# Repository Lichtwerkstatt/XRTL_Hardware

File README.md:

# XRTL_Hardware
Welcome to the XRTL Hardware repository! If you are trying to add actuators, sensors or cameras to your setup, you have come to the right place. You can jump right in and start building or head over to our [wiki](https://github.com/Lichtwerkstatt/XRTL_Hardware/wiki) for basic guides and more information on how to get your hardware to talk to your servers.

If you are instead looking for the software to build some servers or maybe some fancy UI, our [software repository](https://github.com/Lichtwerkstatt/XRTL_SPA) might be the right place for you.

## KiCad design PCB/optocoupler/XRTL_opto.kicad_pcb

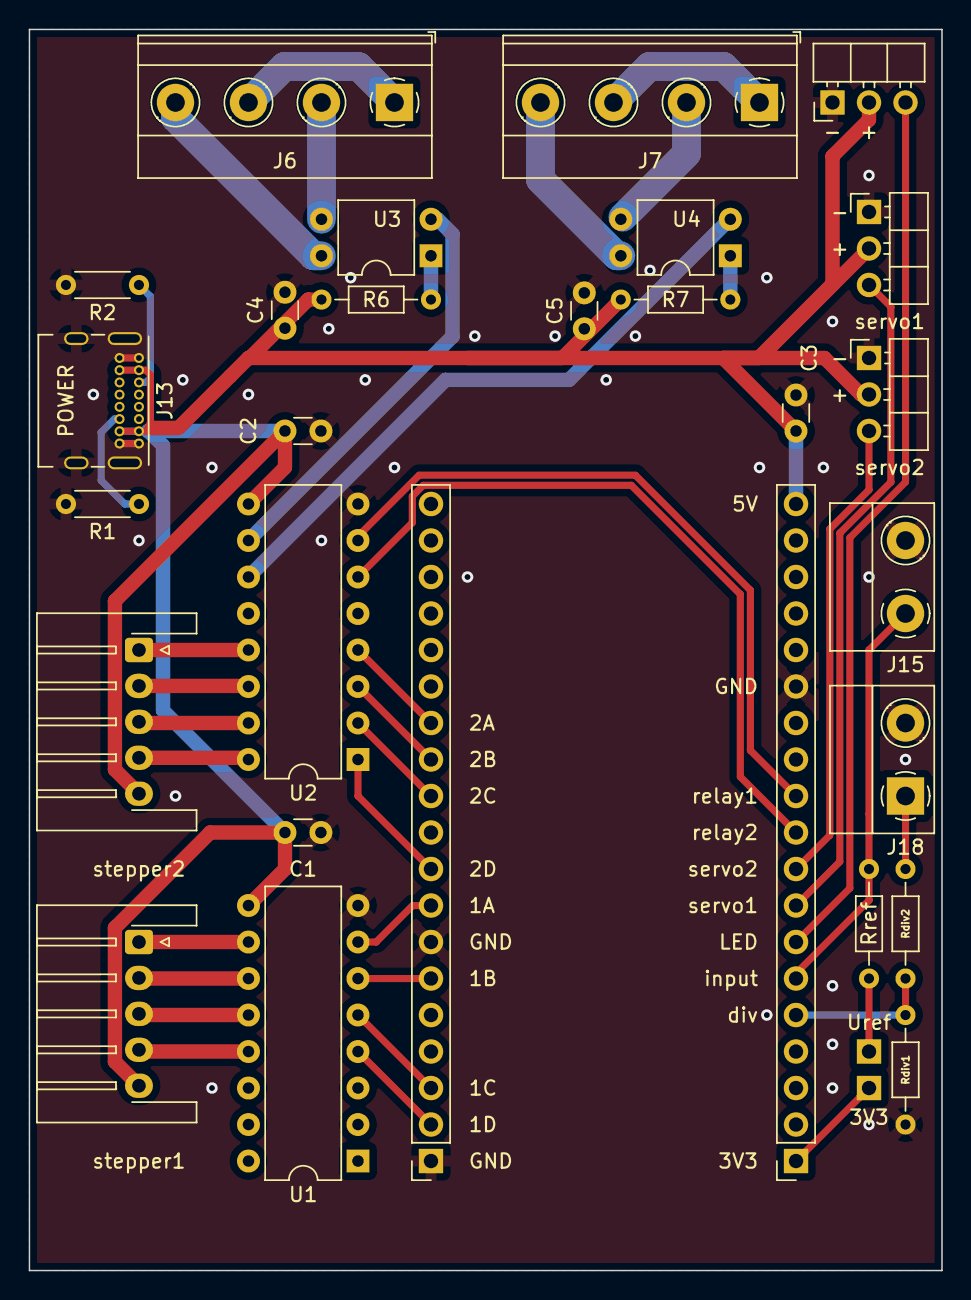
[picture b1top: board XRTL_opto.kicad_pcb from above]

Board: 2 copper layers, 63.5 x 86.4 mm, 30 parts (0 on the bottom side), 40 nets.

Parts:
3V3: conn; PinHeader_1x01_P2.54mm_Vertical
C1, C2, C3, C4, C5: 100n; C_Disc_D3.0mm_W1.6mm_P2.50mm
J2: stepper1; JST_XH_S5B-XH-A-1_1x05_P2.50mm_Horizontal
J3: stepper2; JST_XH_S5B-XH-A-1_1x05_P2.50mm_Horizontal
J4: ESP32 right; PinSocket_1x19_P2.54mm_Vertical
J5: ESP32 left; PinSocket_1x19_P2.54mm_Vertical
J6: relay2; TerminalBlock_Phoenix_MKDS-1,5-4-5.08_1x04_P5.08mm_Horizont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
J7: relay1; TerminalBlock_Phoenix_MKDS-1,5-4-5.08_1x04_P5.08mm_Horizont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
J10: servo1; PinHeader_1x03_P2.54mm_Horizontal
J11: servo2; PinHeader_1x03_P2.54mm_Horizontal
J12: infoLED; PinHeader_1x03_P2.54mm_Horizontal
J13: USBC_5V_3A_input; USB_C_Receptacle_GCT_USB4085
J15: input; TerminalBlock_Phoenix_MKDS-1,5-2-5.08_1x02_P5.08mm_Horizont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
J18: divider; TerminalBlock_Phoenix_MKDS-1,5-2-5.08_1x02_P5.08mm_Horizont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
R1, R2: 5.1k; R_Axial_DIN0204_L3.6mm_D1.6mm_P5.08mm_Horizontal
R6, R7: 511; R_Axial_DIN0204_L3.6mm_D1.6mm_P7.62mm_Horizontal
Rdiv1, Rdiv2: 3.00k; R_Axial_DIN0204_L3.6mm_D1.6mm_P7.62mm_Horizontal
Rref: 3.00k; R_Axial_DIN0204_L3.6mm_D1.6mm_P7.62mm_Horizontal
U1, U2: TBD62003; DIP-16_W7.62mm
U3, U4: TLP3553A; DIP-4_W7.62mm
Uref: Uref; PinHeader_1x01_P2.54mm_Vertical

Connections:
+3V3: 3V3.1, J4.1
+5V: C1.1, C2.1, C3.1, C4.1, C5.1, J2.5, J3.5, J4.19, J10.2, J11.2, J12.2, J13.A4 (VBUS), J13.A9 (VBUS), J13.B4 (VBUS), J13.B9 (VBUS), R6.1, R7.1, U1.9 (COM), U2.9 (COM)
GND: C1.2, C2.2, C3.2, C4.2, C5.2, J4.14, J5.1, J5.7, J10.1, J11.1, J12.1, J13.A1 (GND), J13.A12 (GND), J13.B1 (GND), J13.B12 (GND), J13.S1 (SHIELD), J15.2, J18.2, R1.2, R2.2, Rdiv1.1, U1.8 (GND), U2.8 (GND)
unnamed: J2.1, U1.10 (O7)
unnamed: J2.2, U1.11 (O6)
unnamed: J2.3, U1.12 (O5)
unnamed: J2.4, U1.13 (O4)
unnamed: J3.1, U2.13 (O4)
unnamed: J3.2, U2.14 (O3)
unnamed: J3.3, U2.15 (O2)
unnamed: J3.4, U2.16 (O1)
unnamed: J6.1, J6.3
unnamed: J6.2, U3.3
unnamed: J6.4, U3.4
unnamed: J7.1, J7.3
unnamed: J7.2, U4.3
unnamed: J7.4, U4.4
unnamed: J13.A5 (CC1), R2.1
unnamed: J13.B5 (CC2), R1.1
unnamed: Rref.2, Uref.1
unnamed: J18.1, Rdiv2.2
unnamed: R6.2, U3.1
unnamed: R7.2, U4.1
driverRelay1: U2.11 (O6), U4.2
driverRelay2: U2.10 (O7), U3.2
infoLED: J4.7, J12.3
input1: J4.6, J15.1, Rref.1
input2: J4.5, Rdiv1.2, Rdiv2.1
relay1: J4.11, U2.7 (I7)
relay2: J4.10, U2.6 (I6)
servo1: J4.8, J10.3
servo2: J4.9, J11.3
stepper1A: J5.8, U1.7 (I7)
stepper1B: J5.6, U1.6 (I6)
stepper1C: J5.3, U1.5 (I5)
stepper1D: J5.2, U1.4 (I4)
stepper2A: J5.13, U2.4 (I4)
stepper2B: J5.12, U2.3 (I3)
stepper2C: J5.11, U2.2 (I2)
stepper2D: J5.9, U2.1 (I1)

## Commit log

2021-11-19 entered legacy files
2021-12-03 Create socketIO-KM100.ino
    control single stepper motor via socketIO
2021-12-06 Update socketIO-KM100.ino
    new features:
    -second stepper motor
    -report state before and after moving
    -save current position to EEPROM before restart
2021-12-13 Update socketIO-KM100.ino
    migrate to non blocking stepper library <AccelStepper.h>
2021-12-13 Create ESP8266_ID25
    Controling an ID25 iris aperture via an ESP8266 using a single stepper motor
2021-12-13 Create socketIO-KM100-ESP8266.ino
    adjusted for use on ESP8266
2021-12-20 Update ESP8266_ID25
    -added settings file via LittleFS
    -saving and loading of settings from flash
    -set automatic WiFi reconnect
2021-12-20 Update ESP8266_ID25
2021-12-20 Update socketIO-KM100.ino
    -settings stored and loaded via LITTLEFS
    -automatic WiFi reconnect
2021-12-20 Update socketIO-KM100-ESP8266.ino
    -store settings in flash via LittleFS
    -automatic WiFi reconnect
2022-01-13 implemented automatic reconnect
2022-01-14 non blocking reconnect
2022-01-20 Create LICENSE
2022-01-20 unified ESP32/ESP8266 programs
2022-01-23 added Workshop Reference Markdown
2022-01-23 extended workshop file
2022-01-23 markdown is so nice! I never knew...
2022-01-24 updated workshop script webserver
2022-01-24 workshop file connectWifi
2022-01-24 workshop scripts MQTT
2022-01-24 found text highlightning
2022-01-24 update highlights
2022-01-25 updated workflow
2022-01-25 updated HTTP client workshop
2022-01-25 updated examples
2022-02-14 put workshop files into dedicated repo
2022-03-07 Update ESP32Cam.ino
    -added debug options for event handler
    -added pan and tilt servos
2022-03-07 Create ID25.ino
    -migrate to ESP32 (ESP8266 still optional)
    -added serial debug to event handler
2022-03-07 Update KM100client.ino
    -added serial debug for event handler
2022-03-07 Create laser.ino
    operate a laser via a relais connected to an ESP32
2022-03-08 Create uploadSettings.ino
    save basic connection details in ESP flash using LittleFS
2022-03-21 unified compounds
    available hardware (servos, stepper, relais) are determined at compile time
    settings can be managed over serial monitor
    options for camera added
2022-03-21 Rename XRTL.ino to scr/template/XRTL.ino
2022-03-21 Rename camera.h to scr/template/camera.h
2022-03-21 Rename functions.h to scr/template/functions.h
2022-03-21 Rename infoLED.h to scr/template/infoLED.h
2022-03-21 Rename relais.h to scr/template/relais.h
2022-03-21 Rename scr/template/XRTL.ino to src/template/XRTL.ino
2022-03-21 Rename scr/template/camera.h to src/template/camera.h
2022-03-21 Rename scr/template/functions.h to src/template/functions.h
2022-03-21 Rename scr/template/infoLED.h to src/template/infoLED.h
2022-03-21 Rename scr/template/relais.h to src/template/relais.h
2022-03-21 Rename servo.h to src/template/servo.h
2022-03-21 Rename settings.h to src/template/settings.h
2022-03-21 Rename socketMod.h to src/template/socketMod.h
2022-03-21 Rename stepper.h to src/template/stepper.h
2022-04-25 Create Info
2022-05-04 Update XRTL.ino
    changes due to newest toolchain in arduino environment
2022-05-04 Update functions.h
    added error handling
2022-05-04 Update settings.h
    -expanded polling method of settings
    -added initialization and slider control of stepper
2022-05-04 Update socketMod.h
    added disconnect method (testing needed)
2022-05-04 Update stepper.h
    added initialization and slider control
2022-05-04 Update functions.h
    fixed hostname
2022-05-24 Add files via upload
    fixed pin assignment
2022-06-21 Add files via upload
    added 'status' event and some minor bug fixes
2022-09-14 redesigned to modular firmware
2022-09-14 added PWM capability to output module
2022-09-15 added triggers for input voltage
2022-09-16 added stream interface to input
2022-09-21 JWT authentication
2022-09-21 default for loading of settings added
2022-09-21 changes to debug function
2022-09-21 re-arranged some serial messages
2022-09-21 renamed variables
2022-09-22 changed methode for connection detection of WiFi
2022-09-25 input conversions added
2022-09-28 updated command handling
2022-09-29 camera module functional
2022-10-02 rework of module management
2022-10-02 bufixes
2022-10-02 bugfixes
2022-10-14 changed string handling
2022-10-21 added option for socket SSL
2022-11-30 fixed bugs in command recognition
2022-11-30 added status messages for input & bug fixes
2022-11-30 refactoring camera controls
2022-12-01 complex commands are now rejected when busy
2022-12-08 updated serial setup
2022-12-08 minor fixes
2022-12-12 minor bugfixes
2022-12-12 fixed camera stream start crashing connection
2022-12-12 small changes in input
2022-12-12 comments
2022-12-16 binary control for servos and steppers
2022-12-19 added frame size to camera status
2022-12-20 changes in command structure
2023-01-06 getting rid of componentId
2023-01-12 code style
2023-01-13 added settings
2023-01-18 added syntax for changing LED color
2023-01-19 violation of input bounds can be relayed to server
2023-01-25 adjusted LED values
2023-02-01 fixed bug in servo/stepper command processing
2023-02-01 added maximum speed for servos
2023-02-02 busy message added to servo
2023-02-03 new servo behavior: power down after movement
2023-02-04 added hold key to servo and stepper
2023-02-05 documentation for template module class
2023-02-07 fixed bug in servo relative movement
2023-02-08 fixed binaryCtrl bug
2023-03-02 added macro module
2023-03-07 finalized macro module
2023-03-07 restructured project layout
2023-03-07 Revert "restructured project layout"
    This reverts commit 241fcb7b4dc829725348e7640a02820c7d57ab7f.
2023-03-07 clean up
2023-03-09 separated input and output modules
2023-03-10 fixed bug in servo init
2023-03-15 automatically merge binaries after build/upload
2023-03-30 changed parameter handling
2023-03-30 adding hooks for custom internal events
2023-04-11 changed command structure
2023-04-11 added new command
2023-04-12 added infoLED to output module
2023-04-13 fixed camera bug
2023-04-14 added pause to macro module
2023-04-14 optimized hook load/save
2023-04-17 build cam firmware
2023-04-17 added waitFor<controlId> key to macro module
2023-04-17 adjusted command order
2023-04-17 fixed macro async conditions
2023-04-18 renamed functions
2023-04-18 reworked PCB layout and added optocoupler option
2023-04-20 changed macro control keys
2023-04-20 PCB updates
2023-04-21 corrected gerber files
2023-05-02 moved servo detachment closer to last step
2023-05-02 re-organized 3D models
2023-05-03 update stepper position before saving
2023-05-08 changed serial menu navigation
2023-05-17 welcome message
2023-05-17 changed settings dialog
2023-05-22 fixed wildcard in custom event trigger
2023-05-23 refactored command keys
2023-05-23 small simplification
2023-06-09 enabled wildcard recognition
2023-06-09 stopped stepper from sending unprompted status
2023-06-09 fixed stepper status logic
2023-06-09 cleaned up macro commands
2023-06-12 added "identify" to servo, stepper and output
2023-06-15 added sloppy workaround for auth in local network
2023-06-20 added local mode for time synchronization
2023-06-20 new build
2023-06-21 refactored time sync
2023-06-21 sending time to server after auth
2023-06-21 cleaned up code
2023-06-21 fixed serial messages
2023-06-21 added counter clockwise cycling for LED
2023-06-21 matched LED cycle direction with motor movement
2023-06-27 restructured code and added annotations
2023-06-27 added annotations
2023-07-06 fixed servo LED bug
2023-07-10 build for cam
2023-07-17 code clean up
2023-07-24 added debug message for camera
2023-07-24 fixed serial message bug
2023-07-24 secured events and changed auth event
2023-07-24 update binaries
2023-07-27 added hardwre failure handling to camera/input
2023-07-27 changed parameter visibility
2023-08-01 updated infoLED patterns
2023-08-01 prepared client for time sync in Auth event
2023-08-01 build for esp32cam
2023-08-03 persistent debug mode
2023-08-03 sanitizing serial input of backspace
2023-08-10 removed unused module methodes
2023-08-24 small bugfixes
2023-08-28 changed default parameters
2023-08-28 added current value to parameter queries
2023-08-28 fixed macro aborting on unexisting state call
2023-08-31 replaced servo library by using ledc
2023-08-31 small changes
2023-09-02 prepare new step system
2023-09-04 changed servo to new duty regime
2023-09-04 cleanup
2023-09-06 added corrected travel time for motors
2023-09-07 fixed wrong camera pin
2023-09-07 annotation
2023-09-11 minor bugfix
2023-09-25 fixed connection bug
2023-09-25 corrected default pin
2023-09-25 comment
2023-09-26 removed duplication
2023-09-26 added capability to resolve host via DNS
2023-09-26 build for espcam
2023-09-26 fixed automatic restart
2023-09-26 nimm das
2023-12-12 Old models
2024-03-27 exposed raw camera driver settings via keys
